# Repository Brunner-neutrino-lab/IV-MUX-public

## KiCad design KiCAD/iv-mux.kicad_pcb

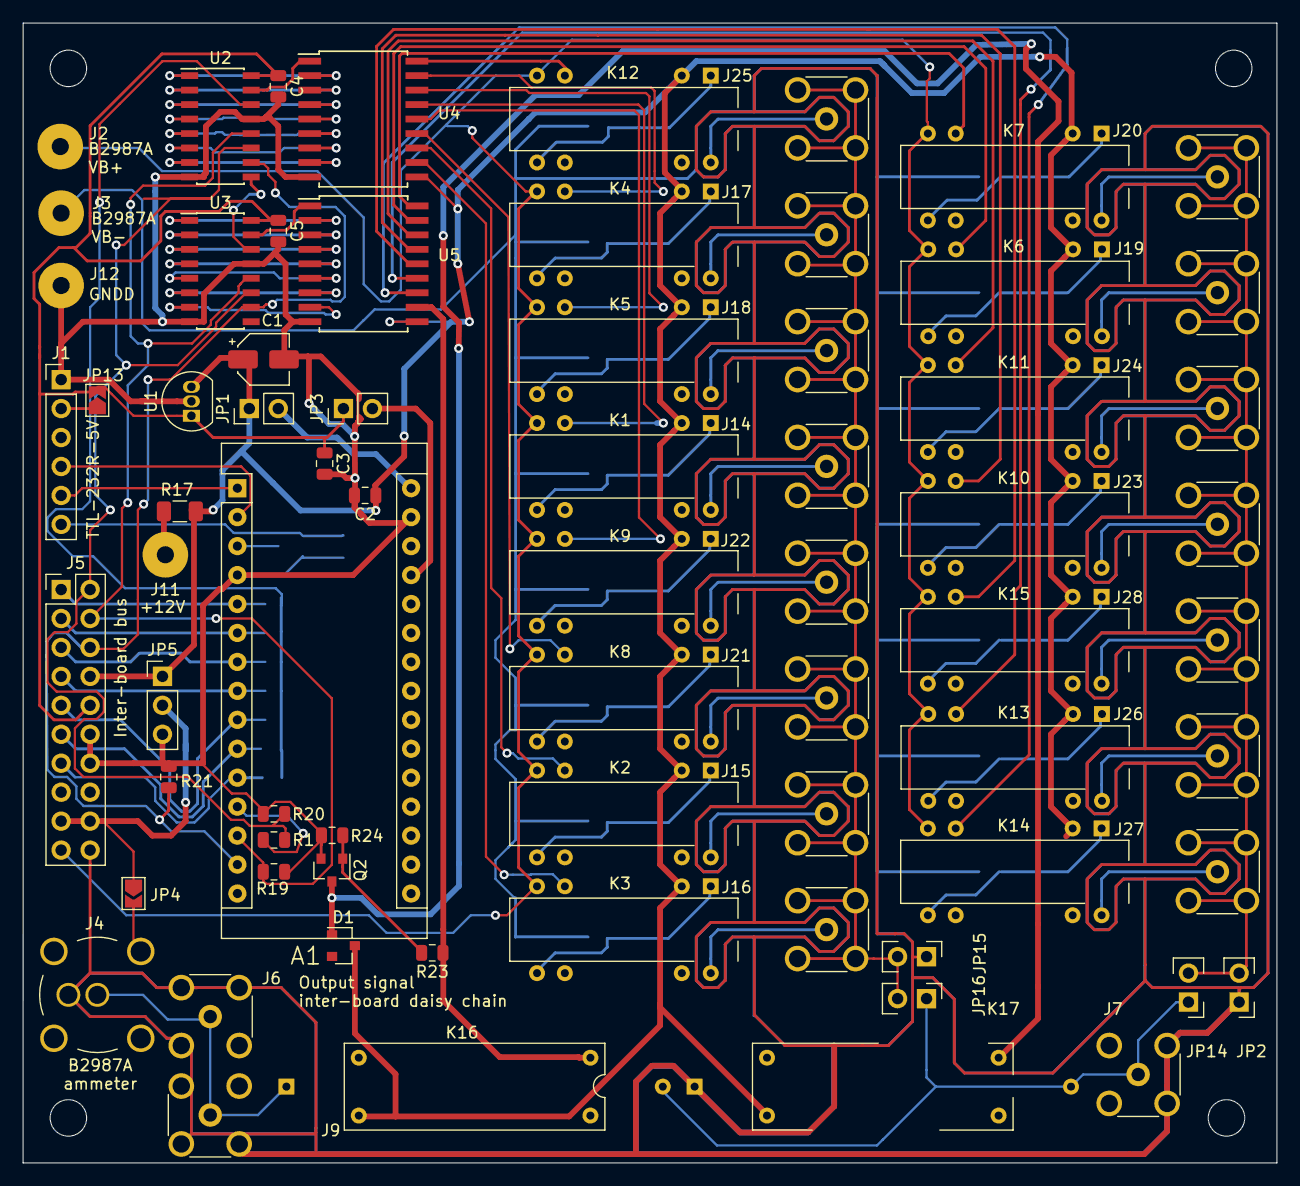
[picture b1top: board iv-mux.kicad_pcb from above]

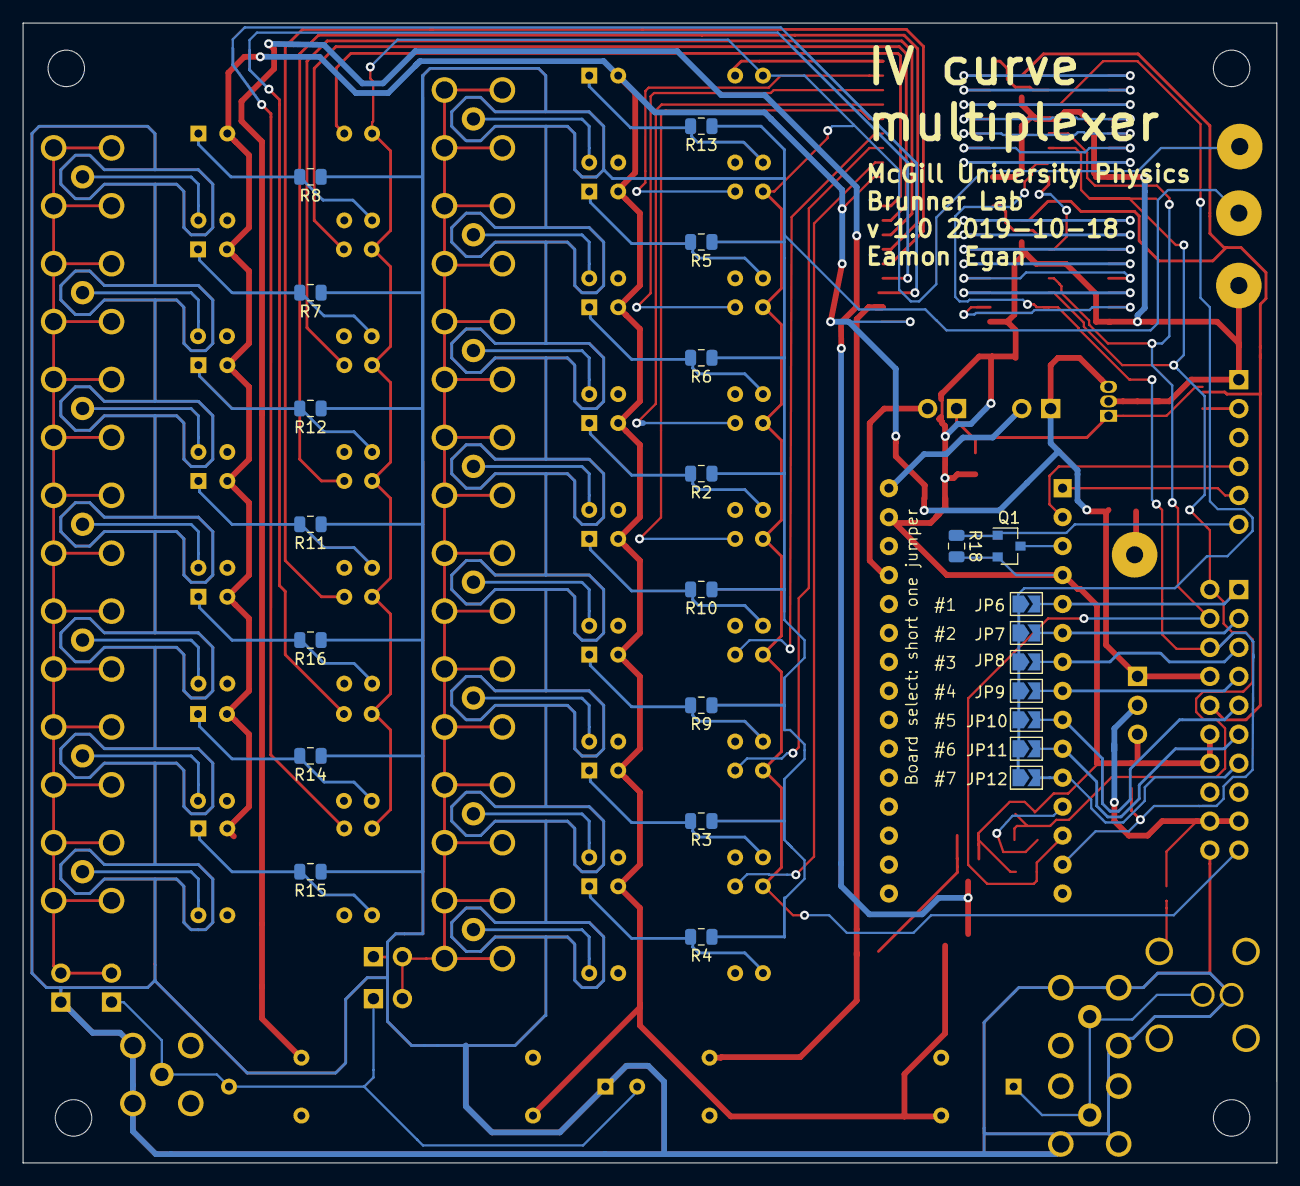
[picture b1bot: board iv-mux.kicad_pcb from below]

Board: 2 copper layers, 110.0 x 100.0 mm, 95 parts (24 on the bottom side), 96 nets.

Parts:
A1: Arduino_Nano_v3.x; Arduino_Nano
C1: CP; CP_Elec_4x3
C2: C; C_0805_2012Metric
C3, C4, C5: 0.1uF; C_0805_2012Metric
D1: BAV70; SOT-23
J1: Conn_01x06_Male; PinHeader_1x06_P2.54mm_Vertical
J2, J3, J11, J12: Conn_01x01_Female; SolderWirePad_1x01_Drill1.5mm
J4: Conn_Triax; BNC_coax_or_triax
J5: Conn_02x10_Odd_Even; PinHeader_2x10_P2.54mm_Vertical
J6, J7, J9, J14, J15, J16, J17, J18, J19, J20, J21, J22, J23, J24, J25, J26, J27, J28: Conn_Coaxial; MCX_Vertical
JP1, JP2, JP3, JP14, JP15, JP16: Jumper_2_Open; PinHeader_1x02_P2.54mm_Vertical
JP4, JP6, JP7, JP8, JP9, JP10, JP11, JP12, JP13: Jumper_2_Open; SolderJumper-2_P1.3mm_Open_TrianglePad1.0x1.5mm
JP5: Jumper_3_Open; PinHeader_1x03_P2.54mm_Vertical
K1, K2, K3, K4, K5, K6, K7, K8, K9, K10, K11, K12, K13, K14, K15: DIP12-2A72-21D; Relay_StandexMeder_DIP_HighProfile_SSmod
K16, K17: HI12-1A85; Relay_StandexMeder_HI
Q1, Q2: 2N7002; SOT-23
R1, R2, R3, R4, R5, R6, R7, R8, R9, R10, R11, R12, R13, R14, R15, R16, R18, R19, R20, R21, R23, R24: R_US; R_0805_2012Metric
R17: R_US; R_1206_3216Metric
U1: L78L05_TO92; TO-92_Inline
U2, U3: 74HC595; SOIC-16_3.9x9.9mm_P1.27mm
U4, U5: ULN2803A; SOIC-18W_7.5x11.6mm_P1.27mm

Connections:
+5V: C3.1, C4.1, C5.1, J5.10, JP3.1, JP13.2, U1.1, U2.16, U3.16
+12V: C1.1, C2.1, D1.3, J5.8, JP1.1, JP5.1, K1.2, K2.2, K3.2, K4.2, K5.2, K6.2, K7.2, K8.2, K9.2, K10.2, K11.2, K12.2, K13.2, K14.2, K15.2, K16.3, K17.3, R17.1, U1.3, U4.10, U5.10
/BIAS RELAYS/BG_OR_SENSE_A: J14.2, J15.2, J16.2, J17.2, J18.2, J21.2, J22.2, J25.2, JP15.2, JP16.2
/BIAS RELAYS/BG_OR_SENSE_B: J19.2, J20.2, J23.2, J24.2, J26.2, J27.2, J28.2, JP2.2, JP14.2
/FTDI_RXD: A1.1, J1.5
/FTDI_TXD: A1.2, J1.4
/SER: JP6.1, JP7.1, JP8.1, JP9.1, JP10.1, JP11.1, JP12.1, U2.14
/SER1: A1.5, J5.1, JP6.2
/SER2: A1.6, J5.3, JP7.2
/SER3: A1.7, J5.5, JP8.2
/SER4: A1.8, J5.7, JP9.2
/SER5: A1.9, J5.9, JP10.2
/SER6: A1.10, J5.11, JP11.2
/SER7: A1.11, J5.13, JP12.2
/Sheet5DB1B453/RCLK: A1.13, J5.4, R19.1, U2.12, U3.12
/Sheet5DB1B453/SRCLK: J5.2, R1.2, R20.1, U2.11, U3.11
/Sheet5DB1B453/~BIAS_ON0: K12.6, U4.18
/Sheet5DB1B453/~BIAS_ON1: K4.6, U4.17
/Sheet5DB1B453/~BIAS_ON2: K5.6, U4.16
/Sheet5DB1B453/~BIAS_ON3: K1.6, U4.15
/Sheet5DB1B453/~BIAS_ON4: K9.6, U4.14
/Sheet5DB1B453/~BIAS_ON5: K8.6, U4.13
/Sheet5DB1B453/~BIAS_ON6: K2.6, U4.12
/Sheet5DB1B453/~BIAS_ON7: K3.6, U4.11
/Sheet5DB1B453/~BIAS_ON8: K7.6, U5.18
/Sheet5DB1B453/~BIAS_ON9: K6.6, U5.17
/Sheet5DB1B453/~BIAS_ON10: K11.6, U5.16
/Sheet5DB1B453/~BIAS_ON11: K10.6, U5.15
/Sheet5DB1B453/~BIAS_ON12: K15.6, U5.14
/Sheet5DB1B453/~BIAS_ON13: K13.6, U5.13
/Sheet5DB1B453/~BIAS_ON14: K14.6, U5.12
/Sheet5DB1B453/~SRCLR: A1.14, J5.6, R21.1, U2.10, U3.10
/VB+: J2.1, J5.19, K1.7, K2.7, K3.7, K4.7, K5.7, K6.7, K7.7, K8.7, K9.7, K10.7, K11.7, K12.7, K13.7, K14.7, K15.7
/VB-: J3.1, J4.3, J5.20, J6.2, J7.2, J9.2, JP2.1, JP15.1, K17.1, R2.1, R3.1, R4.1, R5.1, R6.1, R7.1, R8.1, R9.1, R10.1, R11.1, R12.1, R13.1, R14.1, R15.1, R16.1
/sheet5DD0BE42/ON: D1.1, K17.5, Q2.3
/sheet5DD0BE42/SENSE_DIRECT: J7.1, JP14.1, JP16.1, K16.2, K17.2
/sheet5DD0BE42/SENSE_SWITCHED: J4.1, J6.1, J9.1, K16.1
/sheet5DD0BE42/~ON: K16.5, R23.1, U5.11
GNDA: J5.17, J5.18, JP4.1, JP5.2
GNDD: A1.4, A1.29, C1.2, C2.2, C3.2, C4.2, C5.2, J1.1, J5.12, J5.14, J12.1, JP5.3, Q1.2, Q2.2, R18.2, R19.2, R20.2, R21.2, R24.2, U1.2, U2.8, U2.13, U3.8, U3.13, U4.9, U5.9
unnamed: A1.3, Q1.3
unnamed: A1.12, R1.1
unnamed: A1.27, JP3.2
unnamed: A1.30, JP1.2
unnamed: J1.2, JP13.1
unnamed: J1.6, Q1.1, R18.1
unnamed: J4.2, JP4.2
unnamed: J11.1, R17.2
unnamed: J14.1, K1.14
unnamed: J15.1, K2.14
unnamed: J16.1, K3.14
unnamed: J17.1, K4.14
unnamed: J18.1, K5.14
unnamed: J19.1, K6.14
unnamed: J20.1, K7.14
unnamed: J21.1, K8.14
unnamed: J22.1, K9.14
unnamed: J23.1, K10.14
unnamed: J24.1, K11.14
unnamed: J25.1, K12.14
unnamed: J26.1, K13.14
unnamed: J27.1, K14.14
unnamed: J28.1, K15.14
unnamed: K1.1, K1.8, R2.2
unnamed: K2.1, K2.8, R3.2
unnamed: K3.1, K3.8, R4.2
unnamed: K4.1, K4.8, R5.2
unnamed: K5.1, K5.8, R6.2
unnamed: K6.1, K6.8, R7.2
unnamed: K7.1, K7.8, R8.2
unnamed: K8.1, K8.8, R9.2
unnamed: K9.1, K9.8, R10.2
unnamed: K10.1, K10.8, R11.2
unnamed: K11.1, K11.8, R12.2
unnamed: K12.1, K12.8, R13.2
unnamed: K13.1, K13.8, R14.2
unnamed: K14.1, K14.8, R15.2
unnamed: K15.1, K15.8, R16.2
unnamed: Q2.1, R23.2, R24.1
unnamed: U2.1, U4.2
unnamed: U2.2, U4.3
unnamed: U2.3, U4.4
unnamed: U2.4, U4.5
unnamed: U2.5, U4.6
unnamed: U2.6, U4.7
unnamed: U2.7, U4.8
unnamed: U2.9, U3.14
unnamed: U2.15, U4.1
unnamed: U3.1, U5.2
unnamed: U3.2, U5.3
unnamed: U3.3, U5.4
unnamed: U3.4, U5.5
unnamed: U3.5, U5.6
unnamed: U3.6, U5.7
unnamed: U3.7, U5.8
unnamed: U3.15, U5.1

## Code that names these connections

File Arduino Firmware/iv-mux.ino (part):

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
// shift register (74HC595) control pinout 
int serPins[boardCount] = {2, 3, 4, 5, 6, 7};
const int SRCLK = 9;                // serial clock 
const int RCLK = 10;                // strobe to active register 
const int SRCLR = 11;               // asynchronous clear (active low)

// For synchronization with IV curves using falling voltage transition
// Note: not on rev 1.0 PCB
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  for (i = 0; i < boardCount; i++)
    pinMode(serPins[i], OUTPUT);

  pinMode(SRCLK, OUTPUT);
  pinMode(RCLK, OUTPUT);
  pinMode(SRCLR, OUTPUT);
  
  digitalWrite(SRCLK, LOW);
  digitalWrite(RCLK, LOW);
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}
#endif

// An array of 16-bit words, one for each board (SER pin)
// active high
// bit 0 = ON0 .. bit 14 = ON14 .. bit 15 = SENSE_ON
uint16_t outState[boardCount];
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  int i, j;
  uint16_t mask;
  for (i = 0, mask = 0x8000; mask; i++, mask >>=1) {
    // set SER pins
    for (j = 0; j < boardCount; j++)
      digitalWrite(serPins[j], 0 != (outState[j] & mask)? HIGH : LOW);

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
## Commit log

2024-08-08 Add files from private repo to new public repo
